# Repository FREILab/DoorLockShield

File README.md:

FreiLab Door Lock Repo
======================

This reposetory contains all the infos about our RFID door look system.

Have a look in PCB and Code folder to get more infos.

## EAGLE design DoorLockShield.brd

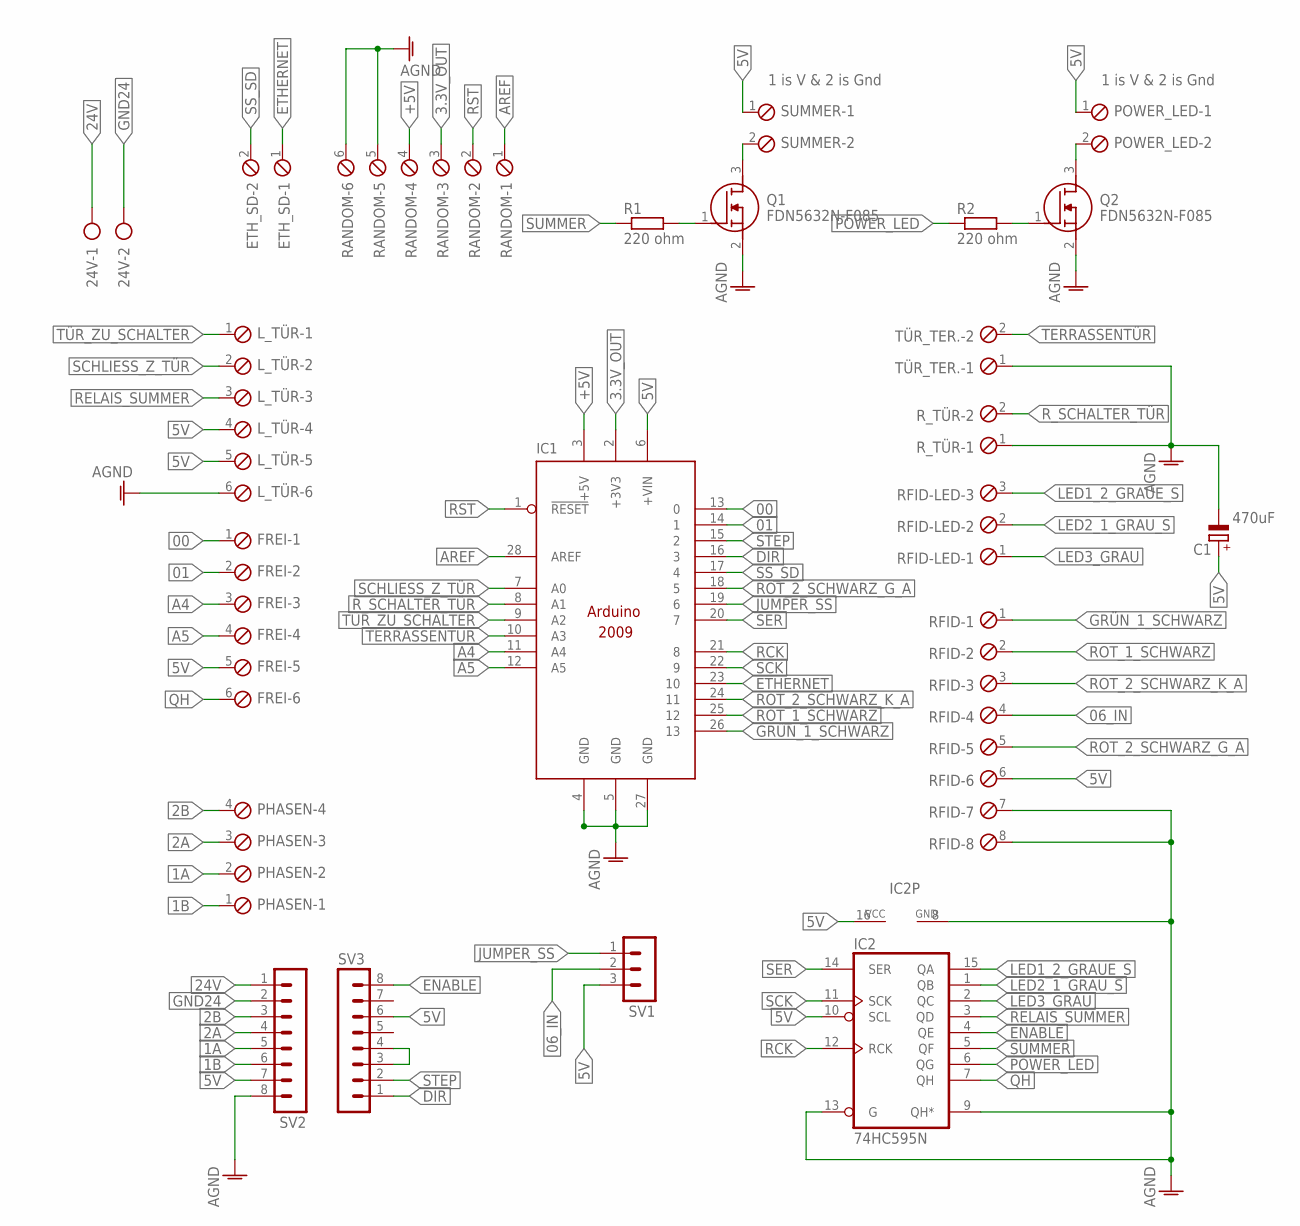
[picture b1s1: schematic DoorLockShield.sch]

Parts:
24V: AK500/2
C1: 470uF; E7,5-16
ETH_SD: MPT2; 2POL254
FREI: MPT6; 6POL254
IC1: ARDUINO2009_12; ARDUINO2009_2
IC2: 74HC595N; DIL16
L_TÜR: MPT6; 6POL254
PHASEN: MPT4; 4POL254
POWER_LED: 1 is V & 2 is Gnd; 2POL254
Q1, Q2: FDN5632N-F085; SOT95P237X122-3N
R1, R2: 220 ohm; R0805
RANDOM: MPT6; 6POL254
RFID: MPT8; 8POL254
RFID-LED: MPT3; 3POL254
R_TÜR: MPT2; 2POL254
SUMMER: 1 is V & 2 is Gnd; 2POL254
SV1: MA03-1
SV2, SV3: MA08-1
TÜR_TER.: MPT2; 2POL254

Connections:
00: FREI.1, IC1.13 (0)
01: FREI.2, IC1.14 (1)
1A: PHASEN.2, SV2.5
1B: PHASEN.1, SV2.6
2A: PHASEN.3, SV2.4
2B: PHASEN.4, SV2.3
3.3V_OUT: IC1.2 (+3V3), RANDOM.3
5V: C1.+, FREI.5, IC1.6 (+VIN), IC2.10 (SCL), IC2.16 (VCC), L_TÜR.4, L_TÜR.5, POWER_LED.1, RFID.6, SUMMER.1, SV1.3, SV2.7, SV3.6
06_IN: RFID.4, SV1.2
24V: 24V.1, SV2.1
+5V: IC1.3 (+5V), RANDOM.4
A4: FREI.3, IC1.11 (A4)
A5: FREI.4, IC1.12 (A5)
AGND: C1.-, IC1.4 (GND), IC1.5 (GND), IC1.27 (GND), IC2.8 (GND), IC2.9 (QH*), IC2.13 (G), L_TÜR.6, Q1.2 (S), Q2.2 (S), RANDOM.5, RANDOM.6, RFID.7, RFID.8, R_TÜR.1, SV2.8, TÜR_TER..1
AREF: IC1.28 (AREF), RANDOM.1
DIR: IC1.16 (3), SV3.1
ENABLE: IC2.4 (QE), SV3.8
ETHERNET: ETH_SD.1, IC1.23 (10)
GND24: 24V.2, SV2.2
GRÜN_1_SCHWARZ: IC1.26 (13), RFID.1
JUMPER_SS: IC1.19 (6), SV1.1
LED1_2_GRAUE_S: IC2.15 (QA), RFID-LED.3
LED2_1_GRAU_S: IC2.1 (QB), RFID-LED.2
LED3_GRAU: IC2.2 (QC), RFID-LED.1
unnamed: Q1.1 (G), R1.2
unnamed: Q2.1 (G), R2.2
unnamed: POWER_LED.2, Q2.3 (D)
unnamed: Q1.3 (D), SUMMER.2
unnamed: SV3.3, SV3.4
POWER_LED: IC2.6 (QG), R2.1
QH: FREI.6, IC2.7 (QH)
RCK: IC1.21 (8), IC2.12 (RCK)
RELAIS_SUMMER: IC2.3 (QD), L_TÜR.3
ROT_1_SCHWARZ: IC1.25 (12), RFID.2
ROT_2_SCHWARZ_G_A: IC1.18 (5), RFID.5
ROT_2_SCHWARZ_K_A: IC1.24 (11), RFID.3
RST: IC1.1 (!RESET), RANDOM.2
R_SCHALTER_TÜR: IC1.8 (A1), R_TÜR.2
SCHLIESS_Z_TÜR: IC1.7 (A0), L_TÜR.2
SCK: IC1.22 (9), IC2.11 (SCK)
SER: IC1.20 (7), IC2.14 (SER)
SS_SD: ETH_SD.2, IC1.17 (4)
STEP: IC1.15 (2), SV3.2
SUMMER: IC2.5 (QF), R1.1
TERRASSENTÜR: IC1.10 (A3), TÜR_TER..2
TÜR_ZU_SCHALTER: IC1.9 (A2), L_TÜR.1

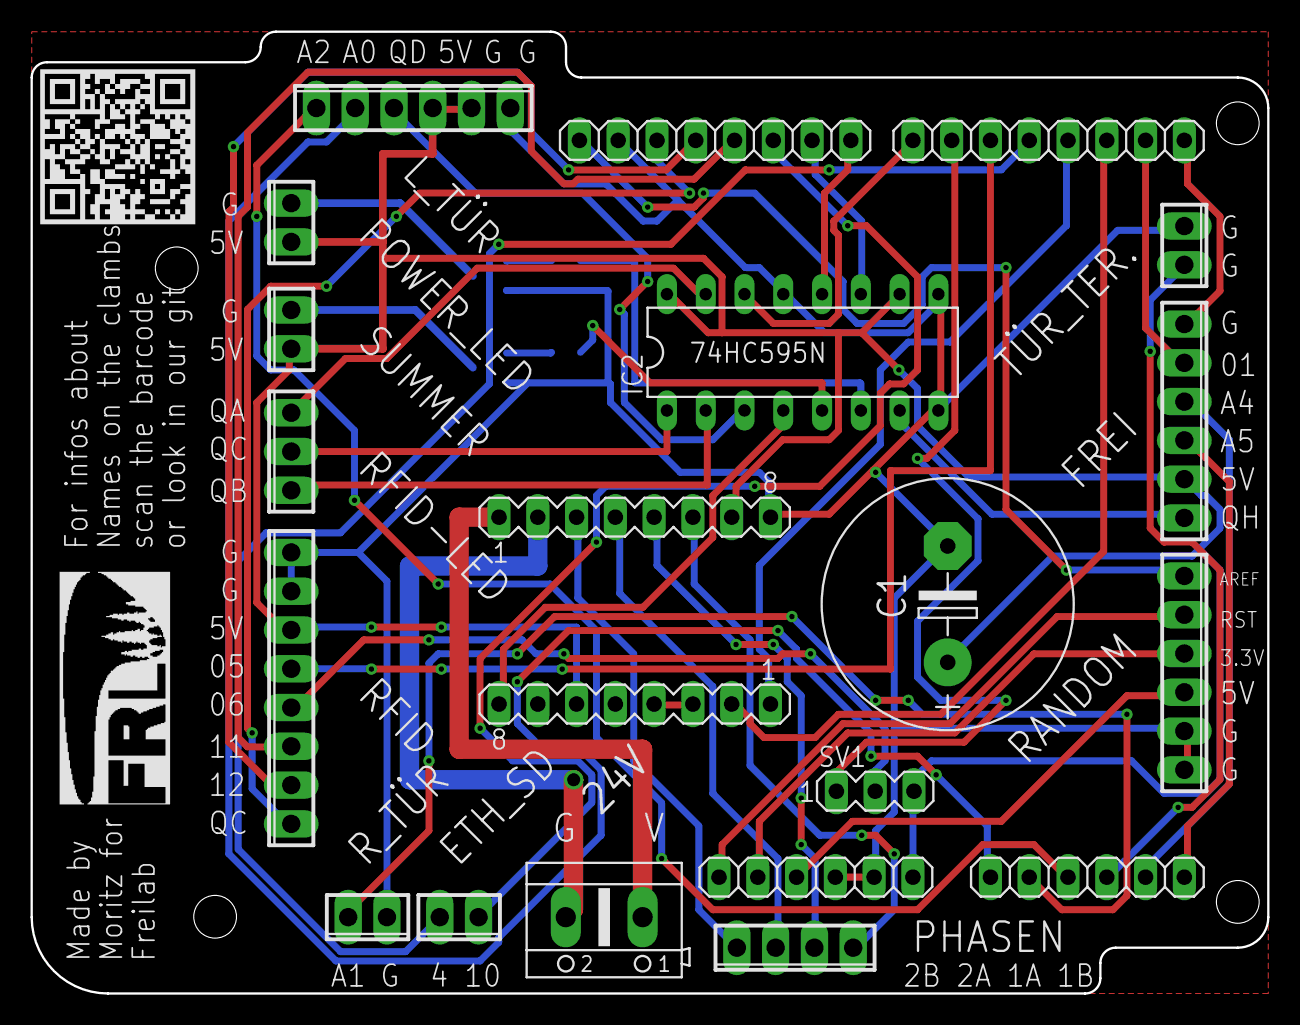
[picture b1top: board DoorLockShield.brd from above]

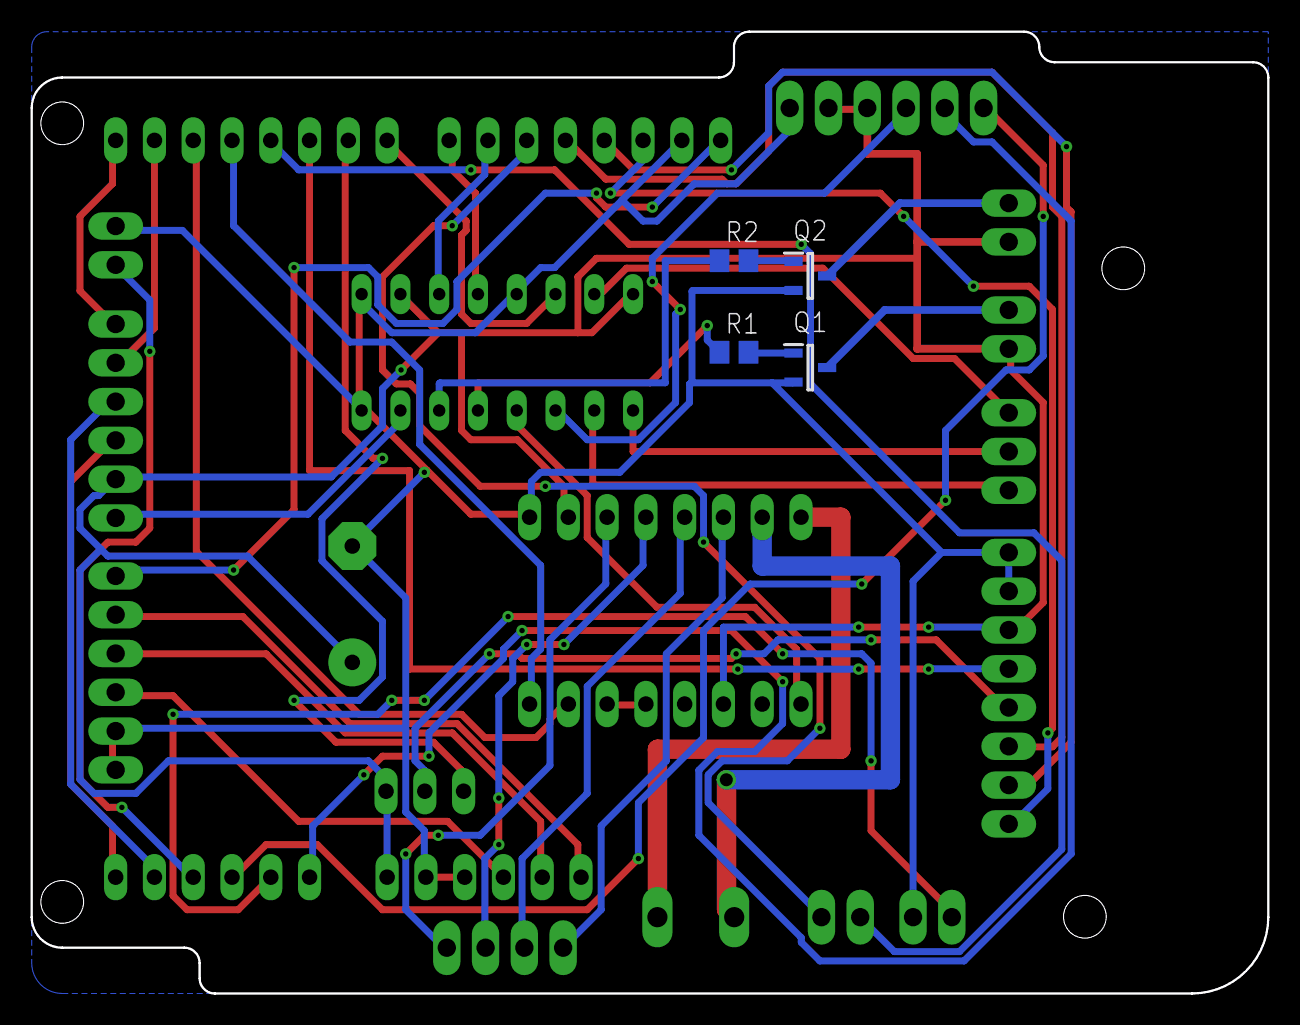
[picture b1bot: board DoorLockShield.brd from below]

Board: 2 copper layers, 81.0 x 63.0 mm, 22 parts (4 on the bottom side), 46 nets.

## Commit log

2019-11-20 added Mess schematic
2019-11-21 added schematic
2019-11-24 finalized schematik
2019-11-26 started to add brd
2019-11-27 changed readme
2019-11-27 added description names on sch and brd
2019-11-27 small design change in brd
2019-12-01 final boeard has to be reviewed
2019-12-01 added freilab bmp logo
2019-12-05 restructure
2019-12-05 added Readme info
2020-02-22 changed naming in board layout to match net names
2023-05-07 restructure content and added code for door shield
2023-05-07 added infos for Hardware
2023-05-07 minor table change
2023-06-08 door is simply working, have to find correct steps for nema 17
2023-06-10 door is working finally
2023-08-17 Looks like door is working now ;)
2023-08-17 fine tuning and clean up
